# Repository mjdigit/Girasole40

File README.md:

# Girasole40
Girasole40はタッチパッドを中央に配置した、30%オーソリニアレイアウトのロープロファイルコンパクトキーボードです。<br/>
The Girasole40 is the self-maid compact lowprofile keyboard which targets 30% ortholinear layout with a touchpad.

Caseless (PCB sandwich mount)

With case (poron gasket mount)

## Parts List

### Parts need to be prepared/purchased

|Part|Quantity|caseless|w/ case|Remarks|
|---|---|---|---|---|
|Wired controller board|1|X|X|RP2040-Zero (w/ pin headers)|
|USB-C cable|1|X|X||
|Choc socket|40|X|X|e.g. Kailh PG1350 KeySwitches Contact (CPG135001S30)|
|Choc V2 switch|40|X|X||
|Keycap|40|X|X||
|Touchpad Module TPS65 (or clone module)|1|X|X|I confirmed [GR-Trackpad65](https://github.com/geek-rabb1t/GR-Trackpad65) works for this keyboard|
|Polycarbonate sheet for touchpad (0.5mm thickness) <br/>or<br/> PVC sheet for touchpad (0.5mm thikness)|1|X|X|Need to be cut to suit TPS65|
|PET double-sided adhesive sheet|1|X|X|Need to be cut to suit TPS65|
|M2 Spacer (3.5mm)|4|X|X|Spacers for between main plate and touchpad mounting plate|
|M2 Spacer (5.0mm)|6|X|X|Spacers for between top plate and bottom plate.|
|M2 screw (3.5mm)|14|X|X|-|
|Additional M2 screw (3.5mm) for caseless|6|X|-|-|
|FPC cable (6pin, 0.5mm pitch, 50mm length)|1|X|X|-|
|Diode|40|X|X|1N4148W|
|Resister 1608 1Kohm|2|X|X|-|
|Capaciter 1608 10uF|1|X|X|-|
|FPC socket (6pin, 0.5mm pitch)|1|X|X|-|
|Rubber feet|6|X|X|-|
|M2 screw (8mm)|4|-|X||
|1.6mm height M2 nut|4|-|X||
|stainless spring (0.4mm wire, d 4mm, L 5mm)|2|-|X||
|poron sheet (L 15mm, W 5mm, d 3mm)|8|-|X||

### Parts need to be ordered/printed
For the plate stacking configuration

|Part|Quantity|caseless|w/ case|Remarks|
|---|---|---|---|---|
|Main PCB|1|X|X|<image src="images/plate-main.png" height="100px"><br/>gerber/main.zip|
|Top Plate|1|X|X|<image src="images/plate-top.png" height="100px"><br/>gerber/top.zip|
|Bottom plate|1|X|-|<image src="images/plate-bottom.png" height="100px"><br/>gerber/bottom.zip|
|Touchpad mounting plate|1|X|X|<image src="images/plate-touchpad.png" height="100px"><br/>gerber/touchpad.zip|
|Top case|1|-|X|<image src="images/case-top.png" height="100px"><br/>case/Girasole40-topcase.step|
|Bottom case|1|-|X|<image src="images/case-bottom.png" height="100px"><br/>case/Girasole40-bottomcase.step|

## Build Guide (Caseless; PCB sandwich mount)
### Assemble passive components on the main PCB
Solder a FPC socket, resisters, a capaciter on front side of the main PCB.

Solder diodes and Choc sockets on back side of the main PCB.

Insert pin headers from back side of the main PCB. Then put RP2040-Zero upside down (place USB-C connector down) from front side.

Solder RP2040-Zero from front side.

On back side, remove off the yello parts of the pin header. Then solder RP2040-Zero from back side.

Shorten pin headers by cut them off.

### Assemble the touchpad
Put a double-sided adhesive sheet on the touchpad module.

Put a Polycarbonate or PVC sheet on the adhesive sheet.

Put a double-sided adhesive sheet on the touchpad mounting plate. Then put the touchpad module on it.

### Construct the keyboard
Place the Top Plate on the Main PCB and put Choc V2 keyswitchs.

Put M2 Spacers on both Top Plate and Main PCB.

Connect the Main PCB and the touchpad module using FPC cable.

Fix the touchpad mounting plate and Main PCB.

Fix the Top Plate and the Bottom Plate. Then put rubber feats.

Note) If you want to build "with case" configuration, please skip this step.

Finally, put keycaps.

## Build Guide (with case)
Please build the keyboard follows "Build Guide (Caseless; PCB sandwich mount)" towards fix the touchpad mounting plate and Main PCB.

Put the spring into the holes on center of the bottom case.

Put the M2 nut into the slots on left & right side of the bottom case.

Put the poron sheet onto the grooves on left & right side of the top & bottom case.

Put the keyboard plate on the bottom case, then put the top case on it.

Fix the top & bottom case by screw holes on left & right side using M2 screw (8mm).

## QMK Firmware
### Firmware binary of default layout (no Vial support)
[girasole40_default.uf2](girasole40_default.uf2)

* Windows Layers
  - Layer 0<br>
  - Layer 1<br>
  - Layer 2<br>
  
* Mac Layers
  - Layer 4<br>
  - Layer 5<br>
  - Layer 6<br>

* Combos
  - Q + W = ESC
  - S + D = Tab
  - O + P = -
  - L + Enter = ;
  - F2 + F3 = F1
  - F10 + F11 = F12
  - 9 + 0 = =

### Vial support

[girasole40_vial.uf2](girasole40_vial.uf2)

Build the Vial-enabled firmware from a Vial-QMK checkout containing the
`qmk_firmware/keyboards/girasole40` directory:

```text
make girasole40:vial
```

Flash `girasole40_vial.uf2`, then open the keyboard in the Vial desktop app.
The keyboard definition is embedded in the firmware, so no JSON import is
required. `layout/girasole40_vial.json` is retained as a readable copy of that
definition.

The Vial keymap keeps the default eight layers and touchpad controls. The
Combo tab provides 16 editable entries; clearing EEPROM restores the seven
original combos as defaults. The custom keycode section exposes drag-scroll
mode and the CPI up/down keys.

Touchpad gestures include tap followed by a second tap-and-hold for dragging,
and a three-finger tap for middle click. The IQS5xx I2C bus runs at 100 kHz for
stable communication.

When Vial asks to unlock the keyboard, hold the top-left and top-right keys
(Q and P in the default base layer). Clear EEPROM once after replacing an
older dynamic-keymap firmware so the Vial keymap and default combos are initialized.

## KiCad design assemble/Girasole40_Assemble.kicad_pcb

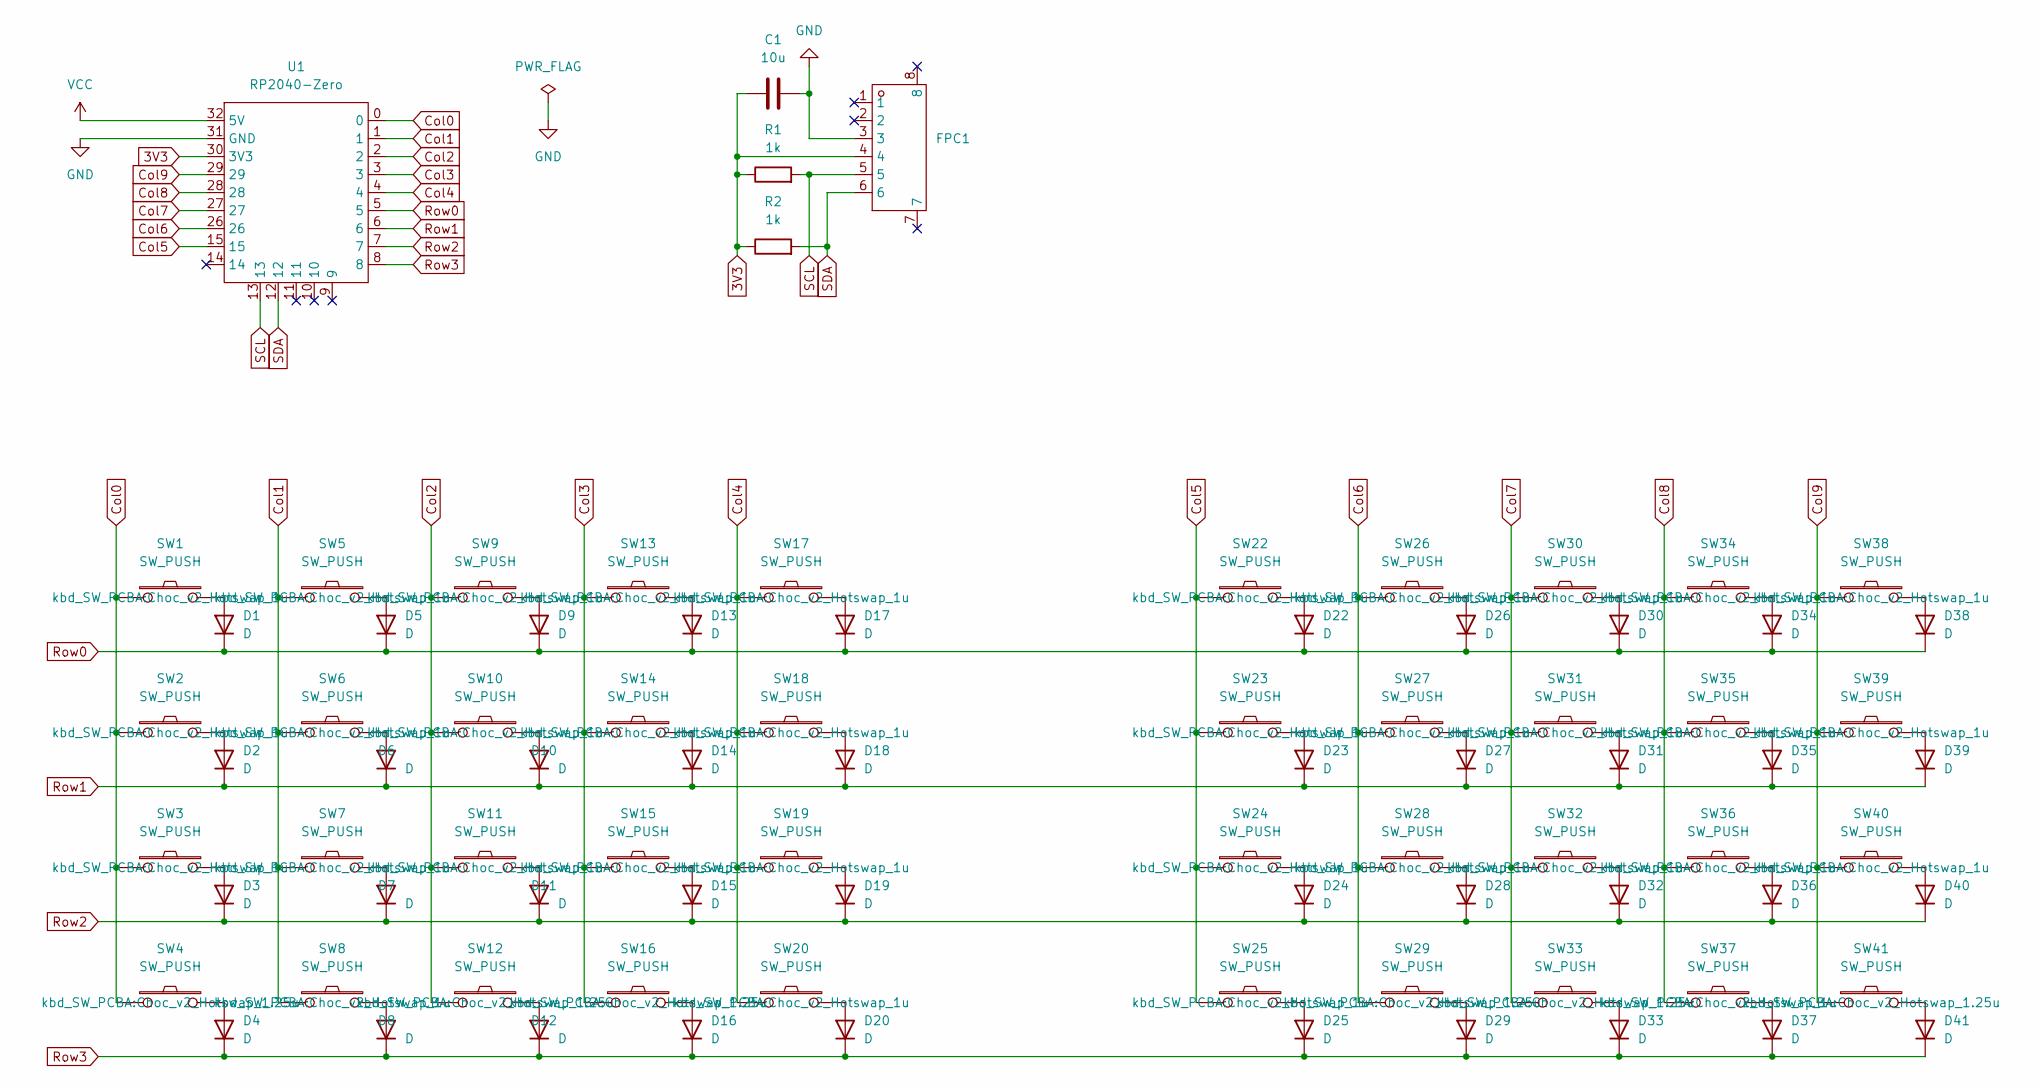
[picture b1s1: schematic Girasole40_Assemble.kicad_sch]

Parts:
C1: 10u; C_0603_1608Metric_Pad1.08x0.95mm_HandSolder
D1, D2, D3, D4, D5, D6, D7, D8, D9, D10, D11, D12, D13, D14, D15, D16, D17, D18, D19, D20, D22, D23, D24, D25, D26, D27, D28, D29, D30, D31, D32, D33, D34, D35, D36, D37, D38, D39, D40, D41: D; Diode_TH_SMD
FPC1: FPC-6p-P0.5mm; Manufacturer Part FPC-05F-6PH20; LCSC Part Name 翻盖式 卧贴 P数:6P 间距:0.5mm
R1, R2: 1k; R_0603_1608Metric_Pad0.98x0.95mm_HandSolder
SW1, SW2, SW3, SW5, SW6, SW7, SW8, SW9, SW10, SW11, SW13, SW14, SW15, SW17, SW18, SW19, SW20, SW22, SW23, SW24, SW25, SW26, SW27, SW28, SW30, SW31, SW32, SW34, SW35, SW36, SW37, SW38, SW39, SW40: SW_PUSH; Choc_v2_Hotswap_1u
SW4, SW12, SW16, SW29, SW33, SW41: SW_PUSH; Choc_v2_Hotswap_1.25u
U1: RP2040-Zero

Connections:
3V3: C1.1, FPC1.4, R1.1, R2.1, U1.30 (3V3)
Col0: SW1.1, SW2.1, SW3.1, SW4.1, U1.0
Col1: SW5.1, SW6.1, SW7.1, SW8.1, U1.1
Col2: SW9.1, SW10.1, SW11.1, SW12.1, U1.2
Col3: SW13.1, SW14.1, SW15.1, SW16.1, U1.3
Col4: SW17.1, SW18.1, SW19.1, SW20.1, U1.4
Col5: SW22.1, SW23.1, SW24.1, SW25.1, U1.15
Col6: SW26.1, SW27.1, SW28.1, SW29.1, U1.26
Col7: SW30.1, SW31.1, SW32.1, SW33.1, U1.27
Col8: SW34.1, SW35.1, SW36.1, SW37.1, U1.28
Col9: SW38.1, SW39.1, SW40.1, SW41.1, U1.29
GND: C1.2, FPC1.3, U1.31 (GND)
unnamed: D1.2 (A), SW1.2
unnamed: D2.2 (A), SW2.2
unnamed: D3.2 (A), SW3.2
unnamed: D4.2 (A), SW4.2
unnamed: D5.2 (A), SW5.2
unnamed: D6.2 (A), SW6.2
unnamed: D7.2 (A), SW7.2
unnamed: D8.2 (A), SW8.2
unnamed: D9.2 (A), SW9.2
unnamed: D10.2 (A), SW10.2
unnamed: D11.2 (A), SW11.2
unnamed: D12.2 (A), SW12.2
unnamed: D13.2 (A), SW13.2
unnamed: D14.2 (A), SW14.2
unnamed: D15.2 (A), SW15.2
unnamed: D16.2 (A), SW16.2
unnamed: D17.2 (A), SW17.2
unnamed: D18.2 (A), SW18.2
unnamed: D19.2 (A), SW19.2
unnamed: D20.2 (A), SW20.2
unnamed: D22.2 (A), SW22.2
unnamed: D23.2 (A), SW23.2
unnamed: D24.2 (A), SW24.2
unnamed: D25.2 (A), SW25.2
unnamed: D26.2 (A), SW26.2
unnamed: D27.2 (A), SW27.2
unnamed: D28.2 (A), SW28.2
unnamed: D29.2 (A), SW29.2
unnamed: D30.2 (A), SW30.2
unnamed: D31.2 (A), SW31.2
unnamed: D32.2 (A), SW32.2
unnamed: D33.2 (A), SW33.2
unnamed: D34.2 (A), SW34.2
unnamed: D35.2 (A), SW35.2
unnamed: D36.2 (A), SW36.2
unnamed: D37.2 (A), SW37.2
unnamed: D38.2 (A), SW38.2
unnamed: D39.2 (A), SW39.2
unnamed: D40.2 (A), SW40.2
unnamed: D41.2 (A), SW41.2
Row0: D1.1 (K), D5.1 (K), D9.1 (K), D13.1 (K), D17.1 (K), D22.1 (K), D26.1 (K), D30.1 (K), D34.1 (K), D38.1 (K), U1.5
Row1: D2.1 (K), D6.1 (K), D10.1 (K), D14.1 (K), D18.1 (K), D23.1 (K), D27.1 (K), D31.1 (K), D35.1 (K), D39.1 (K), U1.6
Row2: D3.1 (K), D7.1 (K), D11.1 (K), D15.1 (K), D19.1 (K), D24.1 (K), D28.1 (K), D32.1 (K), D36.1 (K), D40.1 (K), U1.7
Row3: D4.1 (K), D8.1 (K), D12.1 (K), D16.1 (K), D20.1 (K), D25.1 (K), D29.1 (K), D33.1 (K), D37.1 (K), D41.1 (K), U1.8
SCL: FPC1.5, R1.2, U1.13
SDA: FPC1.6, R2.2, U1.12
VCC: U1.32 (5V)

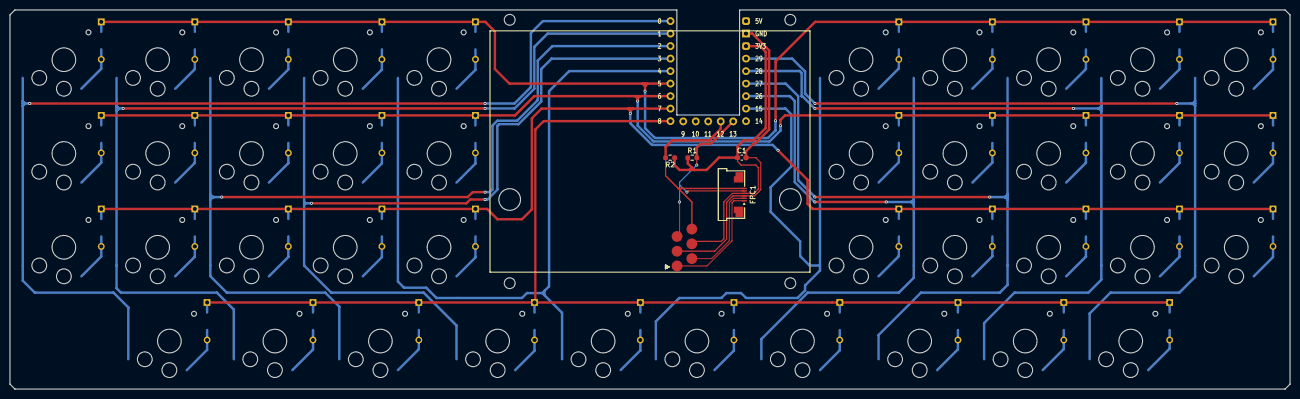
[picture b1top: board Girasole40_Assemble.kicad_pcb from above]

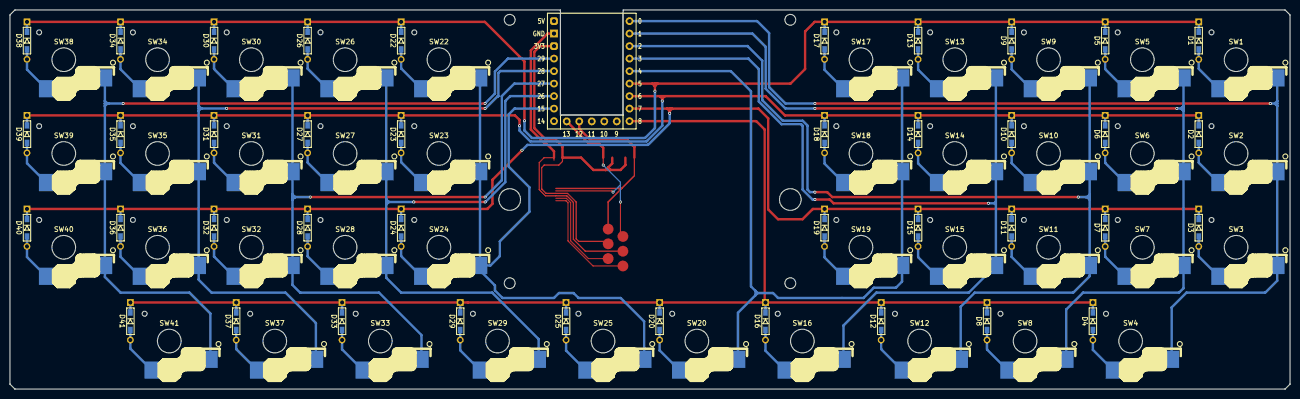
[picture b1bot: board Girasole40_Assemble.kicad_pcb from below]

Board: 2 copper layers, 260.0 x 77.0 mm, 91 parts (41 on the bottom side), 58 nets.

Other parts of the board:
Ref**: M2_ScrewHole
Ref**#2, Ref**#4, Ref**#5: M2_ScrewHole
Ref**#3, Ref**#6: M2_SpacerHole

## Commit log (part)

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2025-12-07 2025-12-07
2025-12-14 Almost completed the layout of parts and wiring
2025-12-29 Have designed PCBs
2025-12-29 Add gerber files
2025-12-29 Add KiCAD assemble files and gerber files (#1)
2026-01-05 Fix the problem silkscreen covers FPC pads
2026-01-06 Added default keymap for QMK firmaware
2026-01-11 Added default key layers for MAC environment.
2026-01-12 Added: CPI adjusting feature
2026-01-24 Add build guide.
2026-02-01 Update default layout - shorten tapping term to 120ms - add F13~F18 keys
2026-02-15 Added bottom case sample step file.
2026-03-03 Topcase prototype 1.
2026-03-03 fix several defects on previous case design
2026-03-07 Evaluation sample 2
2026-03-28 Update build guide.
2026-03-28 Added Keyboard case. (#2)
    * Update build guide.
2026-03-28 Add LICENSE file.
2026-06-13 Change from Combo(A, S) to Combo(S, D) for Tab key
